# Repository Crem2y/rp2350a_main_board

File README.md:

# RP2350A Main Board

A general-purpose RP2350A-based board, originally designed for the [Pico Console V2](https://github.com/Crem2y/pico-console-v2) project.

The board integrates external Flash, PSRAM, and a microSD card slot, with GPIO access through standard 2.54 mm pin headers.

## Specifications

- **MCU:** Raspberry Pi RP2350A
- **Flash:** 1-16 MB
- **PSRAM:** 1-16 MB
- **Power inputs:** VUSB, VBAT, VIN (2.0-5.5 V)
- **Debug:** SWD interface
- **GPIO:** Dual 2.54 mm pin headers (2x12 2.54mm)
- **Additional features:** Onboard LED, microSD connector

## Pinout

## Schematics

## PCB

## Design Files

- **EDA:** KiCad 9.0
- PCB design and schematic source files are available in this repository.

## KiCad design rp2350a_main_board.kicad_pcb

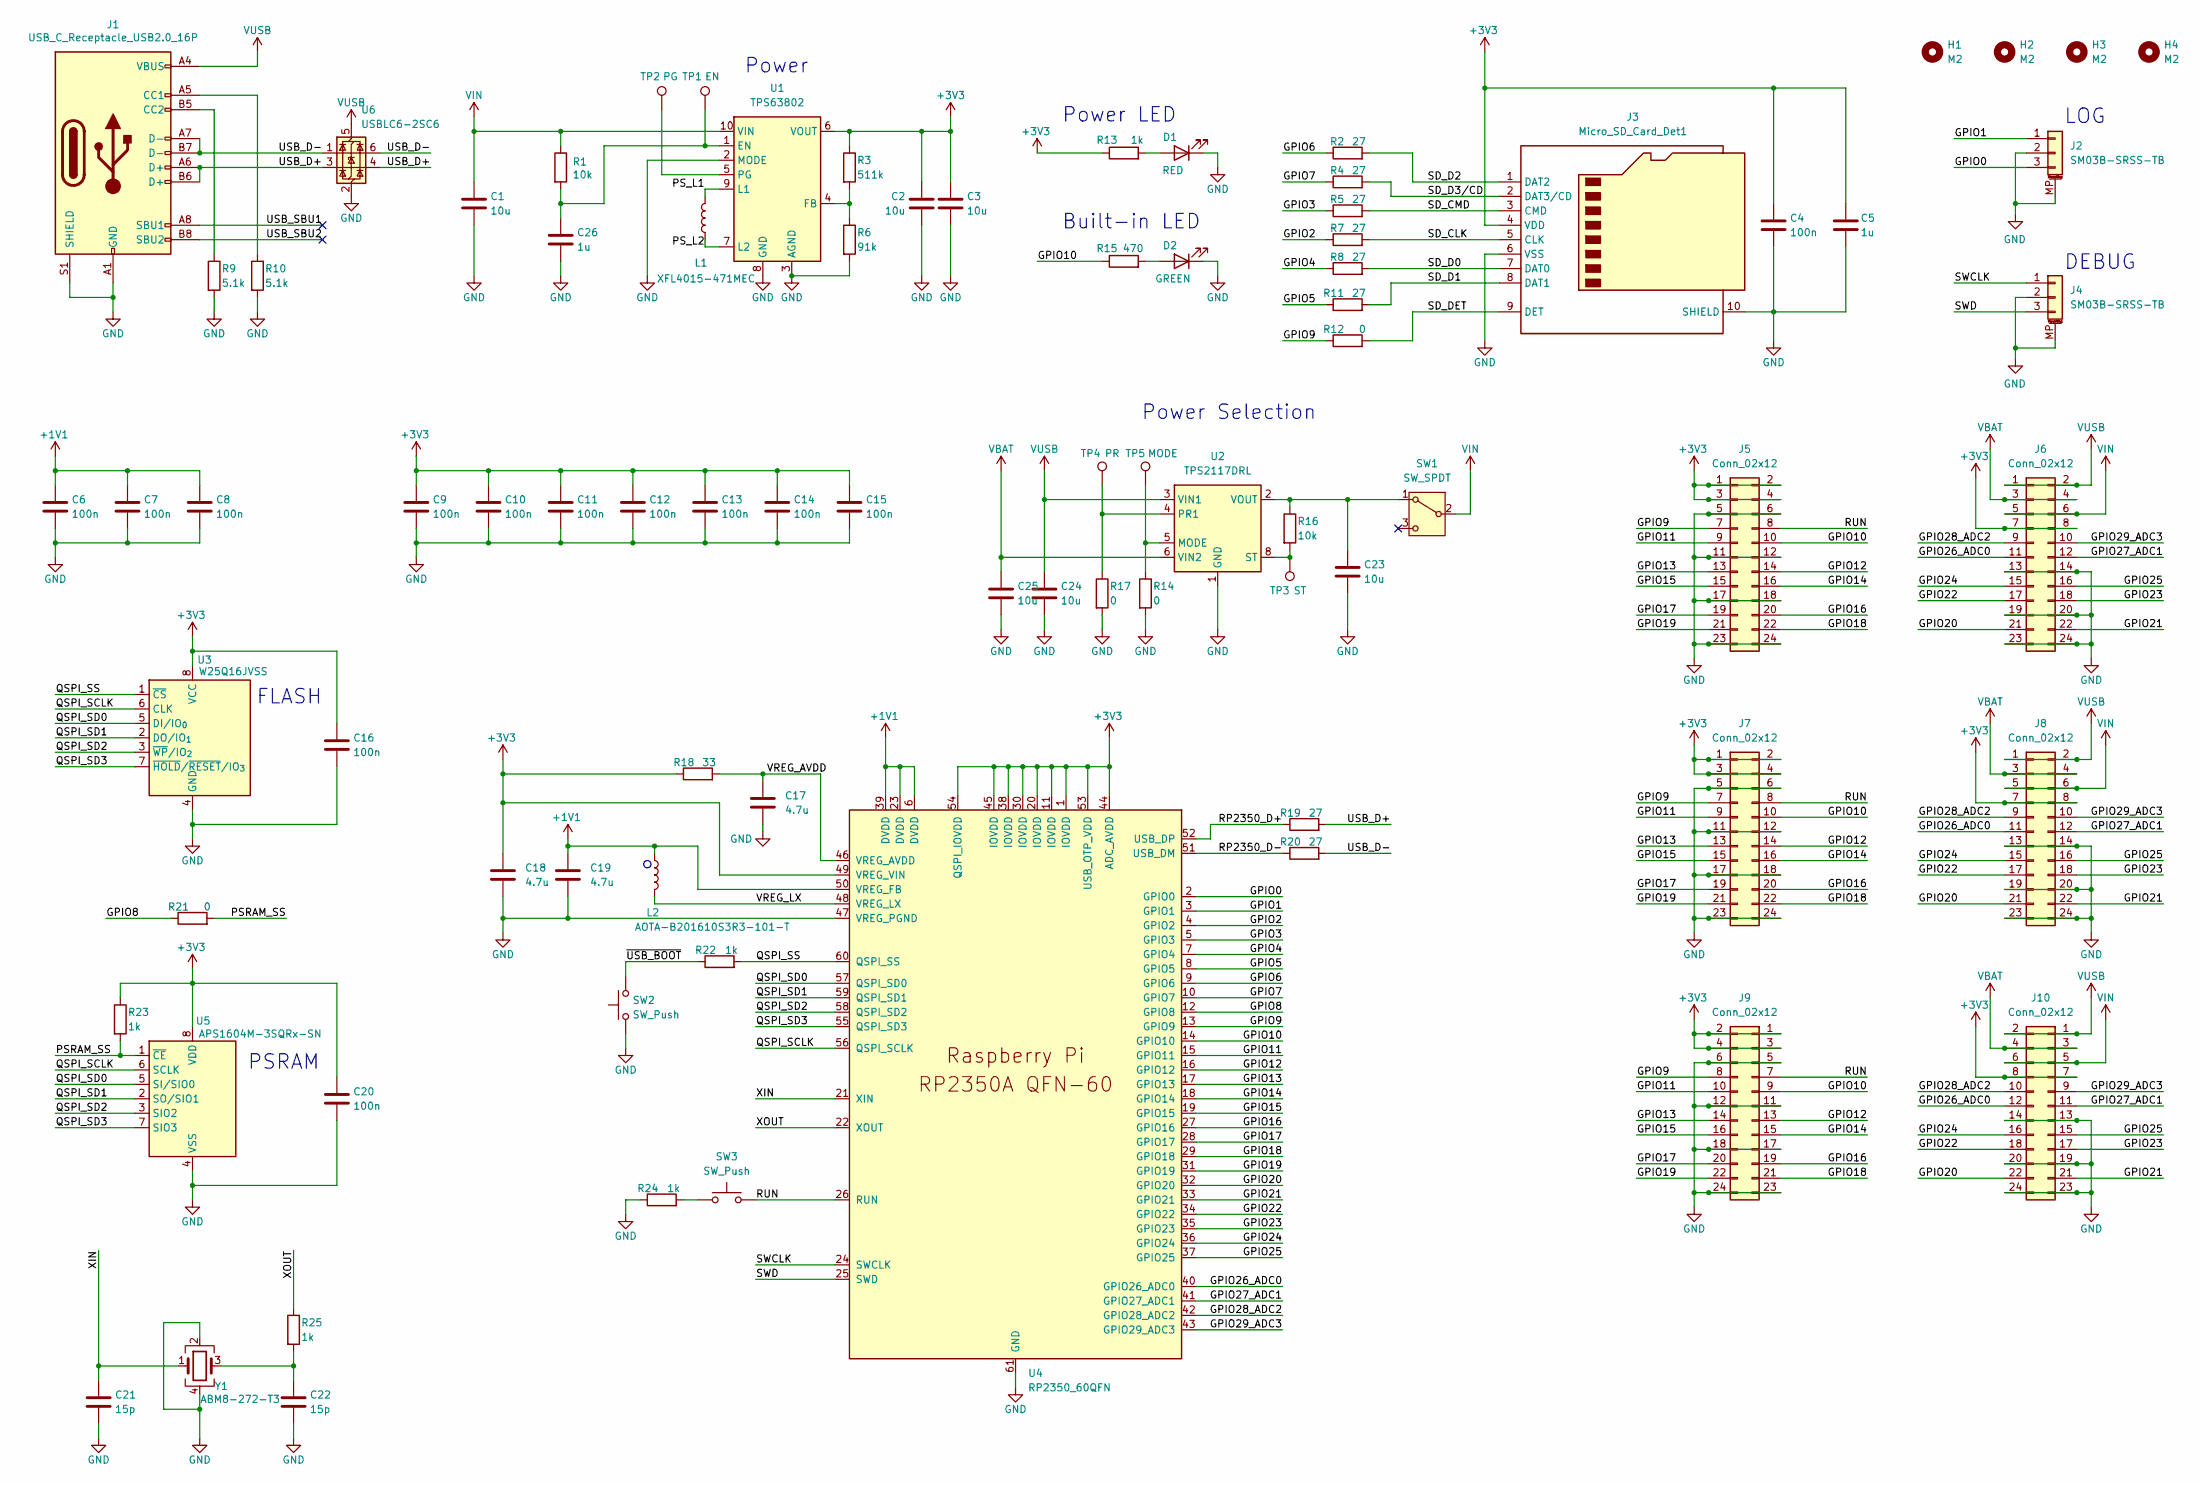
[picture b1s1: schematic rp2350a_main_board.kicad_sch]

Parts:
C1, C2, C3, C23, C24, C25: 10u; C_0603_1608Metric_Pad1.08x0.95mm_HandSolder
C4, C6, C7, C8, C9, C10, C11, C12, C13, C14, C15, C16, C20: 100n; C_0402_1005Metric_Pad0.74x0.62mm_HandSolder
C5, C26: 1u; C_0402_1005Metric_Pad0.74x0.62mm_HandSolder
C17, C18, C19: 4.7u; C_0603_1608Metric_Pad1.08x0.95mm_HandSolder
C21, C22: 15p; C_0402_1005Metric_Pad0.74x0.62mm_HandSolder
D1: RED; LED_0805_2012Metric_Pad1.15x1.40mm_HandSolder
D2: GREEN; LED_0805_2012Metric_Pad1.15x1.40mm_HandSolder
H1, H2, H3, H4: M2; MountingHole_2.2mm_M2
J1: USB_C_Receptacle_USB2.0_16P; USB_C_Receptacle_HRO_TYPE-C-31-M-12
J2, J4: SM03B-SRSS-TB; JST_SH_SM03B-SRSS-TB_1x03-1MP_P1.00mm_Horizontal
J3: Micro_SD_Card_Det1; microSD_HC_Hirose_DM3AT-SF-PEJM5
J5, J6: Conn_02x12; PinSocket_2x12_P2.54mm_Vertical
J7, J8, J9, J10: Conn_02x12; PinSocket_2x12_P2.54mm_Vertical_SMD
L1: XFL4015-471MEC; Inductor_SMD_L_4.0x4.0_H1.5
L2: AOTA-B201610S3R3-101-T; L_pol_2016
R1, R16: 10k; R_0402_1005Metric_Pad0.72x0.64mm_HandSolder
R2, R4, R5, R7, R8, R11, R19, R20: 27; R_0402_1005Metric_Pad0.72x0.64mm_HandSolder
R3: 511k; R_0402_1005Metric_Pad0.72x0.64mm_HandSolder
R6: 91k; R_0402_1005Metric_Pad0.72x0.64mm_HandSolder
R9, R10: 5.1k; R_0402_1005Metric_Pad0.72x0.64mm_HandSolder
R12, R14, R17, R21: 0; R_0402_1005Metric_Pad0.72x0.64mm_HandSolder
R13, R22, R23, R24, R25: 1k; R_0402_1005Metric_Pad0.72x0.64mm_HandSolder
R15: 470; R_0402_1005Metric_Pad0.72x0.64mm_HandSolder
R18: 33; R_0603_1608Metric_Pad0.98x0.95mm_HandSolder
SW1: SW_SPDT; SW_SPDT_CK_JS102011SAQN
SW2, SW3: SW_Push; SW_Push_1P1T_NO_Vertical_Wuerth_434133025816
TP1: EN; TestPoint_Pad_D1.0mm
TP2: PG; TestPoint_Pad_D1.0mm
TP3: ST; TestPoint_Pad_D1.0mm
TP4: PR; TestPoint_Pad_D1.0mm
TP5: MODE; TestPoint_Pad_D1.0mm
U1: TPS63802
U2: TPS2117DRL; SOT-583-8
U3: W25Q16JVSS; SOIC-8_5.3x5.3mm_P1.27mm
U4: RP2350_60QFN; QFN-60-1EP_7x7mm_P0.4mm_EP3.4x3.4mm; LCSC PN C42411118
U5: APS1604M-3SQRx-SN; SOIC-8_3.9x4.9mm_P1.27mm
U6: USBLC6-2SC6; SOT-23-6
Y1: ABM8-272-T3; Crystal_SMD_3225-4Pin_3.2x2.5mm; LCSC PN C20625731

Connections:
+1V1: C6.1, C7.1, C8.1, C19.1, L2.1, U4.6 (DVDD), U4.23 (DVDD), U4.39 (DVDD), U4.50 (VREG_FB)
+3V3: C2.1, C3.1, C4.1, C5.1, C9.1, C10.1, C11.1, C12.1, C13.1, C14.1, C15.1, C16.1, C18.1, C20.1, J3.4 (VDD), J5.1, J5.2, J5.3, J5.4, J6.7, J6.8, J7.1, J7.2, J7.3, J7.4, J8.7, J8.8, J9.1, J9.2, J9.3, J9.4, J10.7, J10.8, R3.1, R13.1, R18.1, R23.1, U1.6 (VOUT), U3.8 (VCC), U4.1 (IOVDD), U4.11 (IOVDD), U4.20 (IOVDD), U4.30 (IOVDD), U4.38 (IOVDD), U4.44 (ADC_AVDD), U4.45 (IOVDD), U4.49 (VREG_VIN), U4.53 (USB_OTP_VDD), U4.54 (QSPI_IOVDD), U5.8 (VDD)
/GPIO0: J2.3, U4.2 (GPIO0)
/GPIO1: J2.1, U4.3 (GPIO1)
/GPIO2: R7.1, U4.4 (GPIO2)
/GPIO3: R5.1, U4.5 (GPIO3)
/GPIO4: R8.1, U4.7 (GPIO4)
/GPIO5: R11.1, U4.8 (GPIO5)
/GPIO6: R2.1, U4.9 (GPIO6)
/GPIO7: R4.1, U4.10 (GPIO7)
/GPIO8: R21.1, U4.12 (GPIO8)
/GPIO9: J5.7, J7.7, J9.8, R12.1, U4.13 (GPIO9)
/GPIO10: J5.10, J7.10, J9.9, R15.1, U4.14 (GPIO10)
/GPIO11: J5.9, J7.9, J9.10, U4.15 (GPIO11)
/GPIO12: J5.14, J7.14, J9.13, U4.16 (GPIO12)
/GPIO13: J5.13, J7.13, J9.14, U4.17 (GPIO13)
/GPIO14: J5.16, J7.16, J9.15, U4.18 (GPIO14)
/GPIO15: J5.15, J7.15, J9.16, U4.19 (GPIO15)
/GPIO16: J5.20, J7.20, J9.19, U4.27 (GPIO16)
/GPIO17: J5.19, J7.19, J9.20, U4.28 (GPIO17)
/GPIO18: J5.22, J7.22, J9.21, U4.29 (GPIO18)
/GPIO19: J5.21, J7.21, J9.22, U4.31 (GPIO19)
/GPIO20: J6.21, J8.21, J10.22, U4.32 (GPIO20)
/GPIO21: J6.22, J8.22, J10.21, U4.33 (GPIO21)
/GPIO22: J6.17, J8.17, J10.18, U4.34 (GPIO22)
/GPIO23: J6.18, J8.18, J10.17, U4.35 (GPIO23)
/GPIO24: J6.15, J8.15, J10.16, U4.36 (GPIO24)
/GPIO25: J6.16, J8.16, J10.15, U4.37 (GPIO25)
/GPIO26_ADC0: J6.11, J8.11, J10.12, U4.40 (GPIO26_ADC0)
/GPIO27_ADC1: J6.12, J8.12, J10.11, U4.41 (GPIO27_ADC1)
/GPIO28_ADC2: J6.9, J8.9, J10.10, U4.42 (GPIO28_ADC2)
/GPIO29_ADC3: J6.10, J8.10, J10.9, U4.43 (GPIO29_ADC3)
/PSRAM_SS: R21.2, R23.2, U5.1 (~CE)
/PS_L1: L1.1, U1.9 (L1)
/PS_L2: L1.2, U1.7 (L2)
/QSPI_SCLK: U3.6 (CLK), U4.56 (QSPI_SCLK), U5.6 (SCLK)
/QSPI_SD0: U3.5 (DI/IO_{0}), U4.57 (QSPI_SD0), U5.5 (SI/SIO0)
/QSPI_SD1: U3.2 (DO/IO_{1}), U4.59 (QSPI_SD1), U5.2 (SO/SIO1)
/QSPI_SD2: U3.3 (~WP/IO_{2}), U4.58 (QSPI_SD2), U5.3 (SIO2)
/QSPI_SD3: U3.7 (~HOLD/~RESET/IO_{3}), U4.55 (QSPI_SD3), U5.7 (SIO3)
/QSPI_SS: R22.2, U3.1 (~CS), U4.60 (QSPI_SS)
/RP2350_D+: R19.1, U4.52 (USB_DP)
/RP2350_D-: R20.1, U4.51 (USB_DM)
/RUN: J5.8, J7.8, J9.7, SW3.2, U4.26 (RUN)
/SD_CLK: J3.5 (CLK), R7.2
/SD_CMD: J3.3 (CMD), R5.2
/SD_D0: J3.7 (DAT0), R8.2
/SD_D1: J3.8 (DAT1), R11.2
/SD_D2: J3.1 (DAT2), R2.2
/SD_D3/CD: J3.2 (DAT3/CD), R4.2
/SD_DET: J3.9 (DET), R12.2
/SWCLK: J4.1, U4.24 (SWCLK)
/SWD: J4.3, U4.25 (SWD)
/USB_D+: J1.A6 (D+), J1.B6 (D+), R19.2, U6.3 (I/O2), U6.4 (I/O2)
/USB_D-: J1.A7 (D-), J1.B7 (D-), R20.2, U6.1 (I/O1), U6.6 (I/O1)
/USB_SBU1: J1.A8 (SBU1)
/USB_SBU2: J1.B8 (SBU2)
/VREG_AVDD: C17.1, R18.2, U4.46 (VREG_AVDD)
/VREG_LX: L2.2, U4.48 (VREG_LX)
/XIN: C21.1, U4.21 (XIN), Y1.1
/XOUT: R25.1, U4.22 (XOUT)
/~USB_BOOT: R22.1, SW2.2
GND: C1.2, C2.2, C3.2, C4.2, C5.2, C6.2, C7.2, C8.2, C9.2, C10.2, C11.2, C12.2, C13.2, C14.2, C15.2, C16.2, C17.2, C18.2, C19.2, C20.2, C21.2, C22.2, C23.2, C24.2, C25.2, C26.2, D1.1 (K), D2.1 (K), J1.A1 (GND), J1.A12 (GND), J1.B1 (GND), J1.B12 (GND), J1.S1 (SHIELD), J2.2, J2.MP (MountPin), J3.6 (VSS), J3.10 (SHIELD), J4.2, J4.MP (MountPin), J5.5, J5.6, J5.11, J5.12, J5.17, J5.18, J5.23, J5.24, J6.13, J6.14, J6.19, J6.20, J6.23, J6.24, J7.5, J7.6, J7.11, J7.12, J7.17, J7.18, J7.23, J7.24, J8.13, J8.14, J8.19, J8.20, J8.23, J8.24, J9.5, J9.6, J9.11, J9.12, J9.17, J9.18, J9.23, J9.24, J10.13, J10.14, J10.19, J10.20, J10.23, J10.24, R6.2, R9.2, R10.2, R14.2, R17.2, R24.1, SW2.1, U1.2 (MODE), U1.3 (AGND), U1.8 (GND), U2.1 (GND), U3.4 (GND), U4.47 (VREG_PGND), U4.61 (GND), U5.4 (VSS), U6.2 (GND), Y1.2, Y1.4
unnamed: C22.1, R25.2, Y1.3
unnamed: D1.2 (A), R13.2
unnamed: D2.2 (A), R15.2
unnamed: J1.A5 (CC1), R10.1
unnamed: J1.B5 (CC2), R9.1
unnamed: R24.2, SW3.1
unnamed: C23.1, R16.1, SW1.1 (A), U2.2 (VOUT), U2.7 (VOUT)
unnamed: C26.1, R1.2, TP1.1, U1.1 (EN)
unnamed: R3.2, R6.1, U1.4 (FB)
unnamed: TP2.1, U1.5 (PG)
unnamed: R14.1, TP5.1, U2.5 (MODE)
unnamed: R17.1, TP4.1, U2.4 (PR1)
unnamed: R16.2, TP3.1, U2.8 (ST)
VBAT: C25.1, J6.3, J6.4, J8.3, J8.4, J10.3, J10.4, U2.6 (VIN2)
VIN: C1.1, J6.5, J6.6, J8.5, J8.6, J10.5, J10.6, R1.1, SW1.2 (B), U1.10 (VIN)
VUSB: C24.1, J1.A4 (VBUS), J1.A9 (VBUS), J1.B4 (VBUS), J1.B9 (VBUS), J6.1, J6.2, J8.1, J8.2, J10.1, J10.2, U2.3 (VIN1), U6.5 (VBUS)

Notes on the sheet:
DEBUG
FLASH
Built-in LED
Power LED
PSRAM
Power
LOG
Power Selection

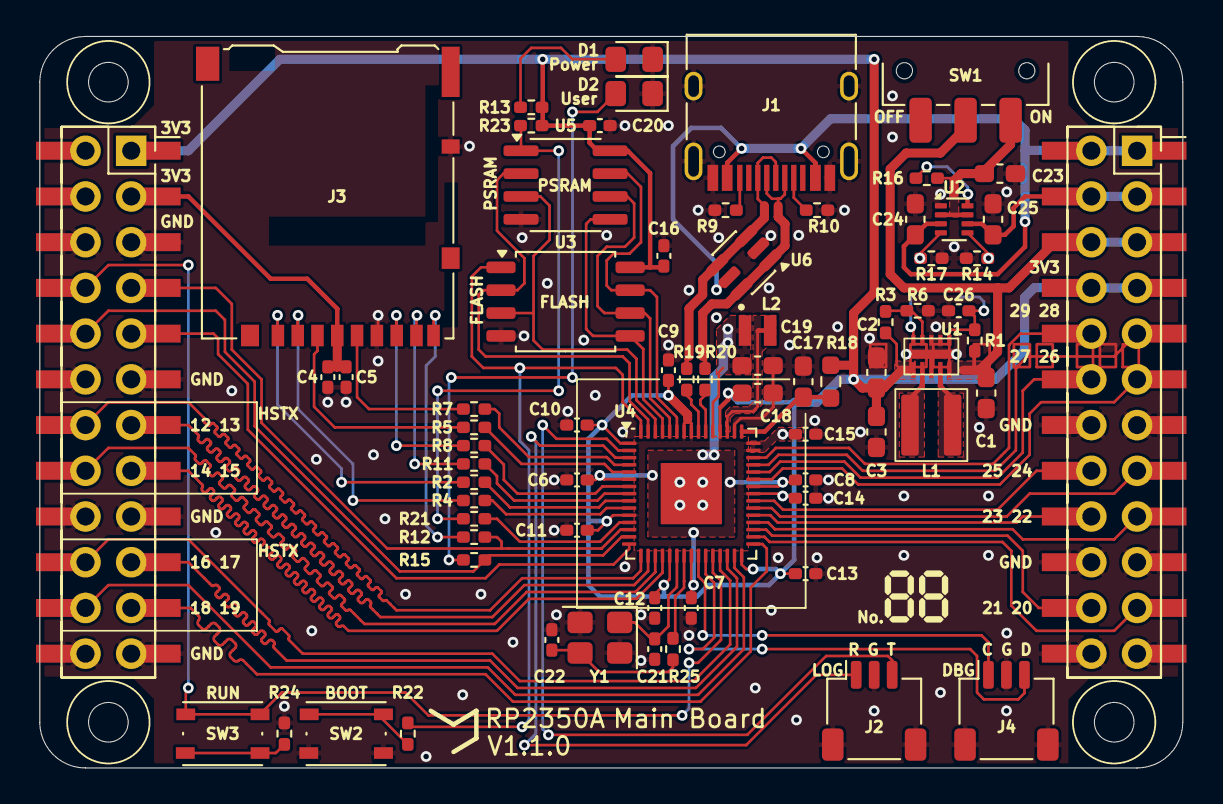
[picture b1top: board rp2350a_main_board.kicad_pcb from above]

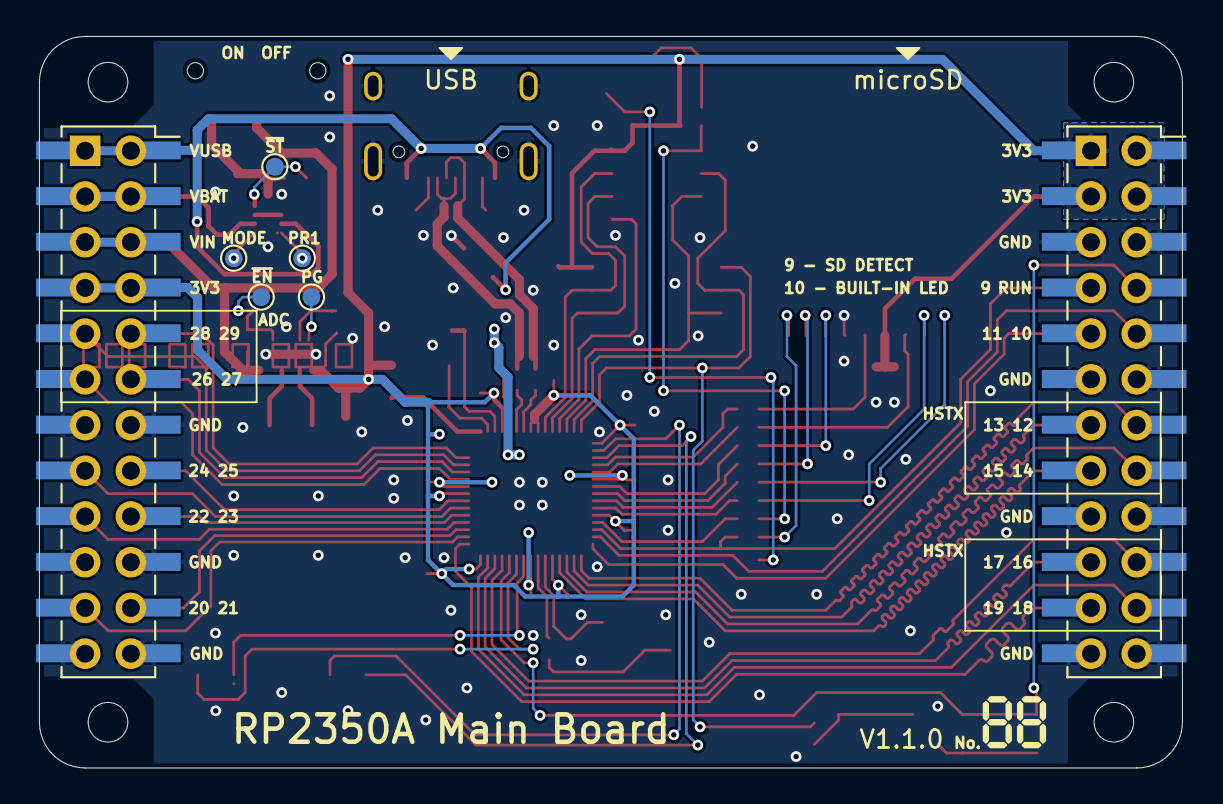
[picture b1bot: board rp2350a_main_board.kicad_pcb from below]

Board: 2 copper layers, 63.5 x 40.6 mm, 84 parts (7 on the bottom side), 77 nets.

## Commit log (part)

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2026-05-16 initial commit (copy from https://github.com/Crem2y/rp2350a_test_board)
2026-05-16 Add footprints
2026-05-16 Add symbol
2026-05-16 V1.0.0
2026-05-16 Clean up component references
2026-05-16 Update BOM list
2026-05-16 Add text, Add part name to L1
2026-05-16 add documentation
